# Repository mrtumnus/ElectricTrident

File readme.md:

Programmable Electric Trident
================================

(Insert pic here)

Programmable LED-lit trident. Intended for use with ATtiny85 (or Arduino) based boards and [Neopixel](https://www.adafruit.com/categories/37) (WS2811/12/12B) RGB LEDs.

Instructions
------------

* Download Adafruit's [NeoPixel](https://github.com/adafruit/Adafruit_NeoPixel) library
* Get the [ATtiny cores](https://code.google.com/p/arduino-tiny/) for Arduino & a [programmer](https://www.adafruit.com/products/46)
* Attach your LED data line to Digital Pin 0
* Attach pushbutton switch to Digital Pin 1
* Enjoy your electric trident

Acknowledgements
------------

Derived from https://github.com/danasf/firefly

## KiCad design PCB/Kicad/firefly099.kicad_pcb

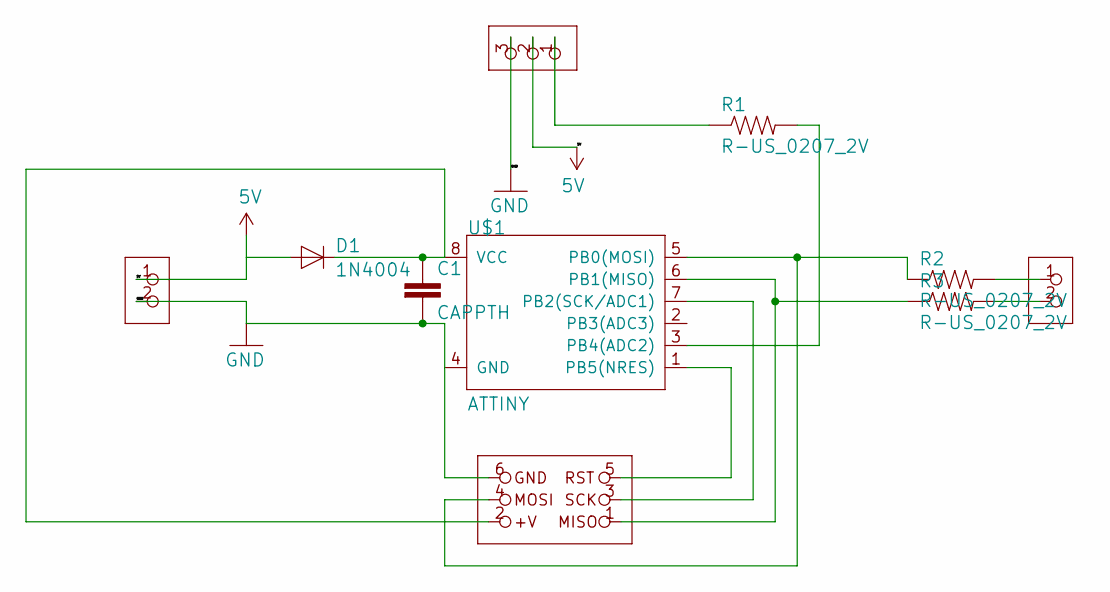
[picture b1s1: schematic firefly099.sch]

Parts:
-,+1: CON_TERMINAL_BLOCK_02-5MM; TERMINAL_BLOCK_2P_5
C1: CAPPTH; CAP-PTH-SMALL
D1: 1N4004; DO41-10
IO1: CON_TERMINAL_BLOCK_02-5MM; TERMINAL_BLOCK_2P_5
J3: CON_HEADER_PRG_AVR_ICSP-PTH; HEADER_PRG_2X03
LED1: CON_TERMINAL_BLOCK_03-5MM; TERMINAL_BLOCK_3P_5
R1, R2, R3: R-US_0207_2V; 0207_2V
U$1: ATTINY; DIP08

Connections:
5V: -,+1.1, D1.A, LED1.2
GND: -,+1.2, C1.2, J3.6 (GND), LED1.3, U$1.4 (GND)
unnamed: C1.1, D1.C, J3.2 (+V), U$1.8 (VCC)
unnamed: IO1.1, R2.2
unnamed: IO1.2, R3.2
unnamed: J3.1 (MISO), R3.1, U$1.6 (PB1(MISO))
unnamed: J3.3 (SCK), U$1.7 (PB2(SCK/ADC1))
unnamed: J3.4 (MOSI), R2.1, U$1.5 (PB0(MOSI))
unnamed: J3.5 (RST), U$1.1 (PB5(NRES))
unnamed: LED1.1, R1.1
unnamed: R1.2, U$1.3 (PB4(ADC2))

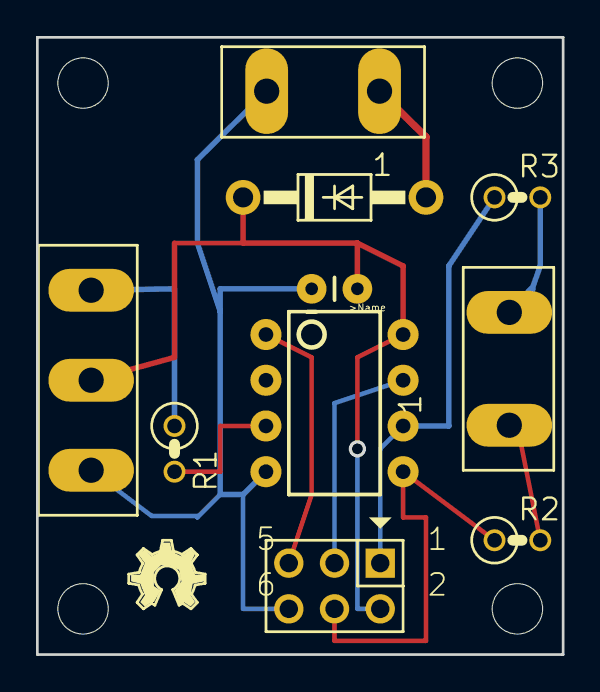
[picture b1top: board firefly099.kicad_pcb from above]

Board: 2 copper layers, 29.2 x 34.3 mm, 15 parts (0 on the bottom side), 11 nets.

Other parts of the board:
@HOLE0, @HOLE1, @HOLE2, @HOLE3: (no value)
U$4: OSHW_FILLX150_NOTEXT

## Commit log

2018-12-20 Moved project file so Arduino IDE won't complain
2018-12-20 Converted project to FastLED library. Some states were removed to fit within an ATTiny85 (currently at 7438 bytes).
2018-12-21 Bumped up LED count to match a typical strand
2018-12-21 Renamed colorFast to colorFill. Some other optimizations
2018-12-21 Changed state ordering; fixed twinkle (still needs some more randomness)
2018-12-21 Reduced NUM_LED to the approxomite number in a jar; added random delay after twinkle
2018-12-21 Created table for colorFirefly(), removing call to sin(). Removed unused variables & renamed some
2018-12-21 Optimized some features. Added random delay for firefly & made it firefly-color
2019-03-20 Added folder & readme for raspberry pi loader for ATTiny85
2019-03-20 Converted eagle files to Kicad format
2019-03-20 Added sine table
2019-03-20 Added schematic for raspberry pi loader
2019-03-22 Added blinky test project for loading with RPi
2019-03-22 Organized PCB files
2019-03-23 Organized a bit
2019-03-23 More organization
2019-03-23 Renamed arduino project to ElectricTridentControl
2019-03-23 Reverted some over-organization
2019-03-23 Re-added files I had accidentally removed
2019-03-23 Removed cap-touch features, replacing with digital input
2019-03-23 Added digital LED output, changed pin mappings, changed LED states
2019-03-23 Something of a trident flashing routine
2019-04-10 Added trident simulator Qt project
2019-04-10 Implemented trident layout
2019-04-10 Randomize initial hue, and constrain to orange tones
2019-04-10 Decoupled animation pieces into separate class, TridentAnimation
2019-04-10 Increased LED diameter, added bolt inner radius, slowed down animation
2019-04-11 Removed .user file
2019-04-11 Randomized pixel drift direction/amount & slowed down
2019-04-11 Added gitignore
2019-04-11 Setup arduino project to use same tridentanimation used by simulator. It builds!
2019-04-11 tridentanimation.h/cpp are now relative references in Qt Creator project (used directly from Arduino/libraries/ElectricTrident/)
2019-04-11 Fixed Qt build - added include path for animation files
2019-04-11 Removed unused variable declarations
2019-04-18 Removed unused ledDir array. Added some bolt color options
2019-04-22 Many improvements to the animation. Fixed mismatch between simulator & FastLED hue usage. Added Sat & Lum/Val randomization and range enforcement.
2019-04-22 Added test animation for mapping LEDs. Created TridentAnimationBase.
2019-04-22 Moved pixel locating into Trident class; now the real trident runs the animation properly for the tines
2019-04-22 Added glowing effect for trident tine tips
2019-12-24 Implemented hex load script
2021-05-04 Added trident animation captured from QT simulator

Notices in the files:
PCB/Kicad/firefly099.kicad_pcb:
CC-BY-SA
